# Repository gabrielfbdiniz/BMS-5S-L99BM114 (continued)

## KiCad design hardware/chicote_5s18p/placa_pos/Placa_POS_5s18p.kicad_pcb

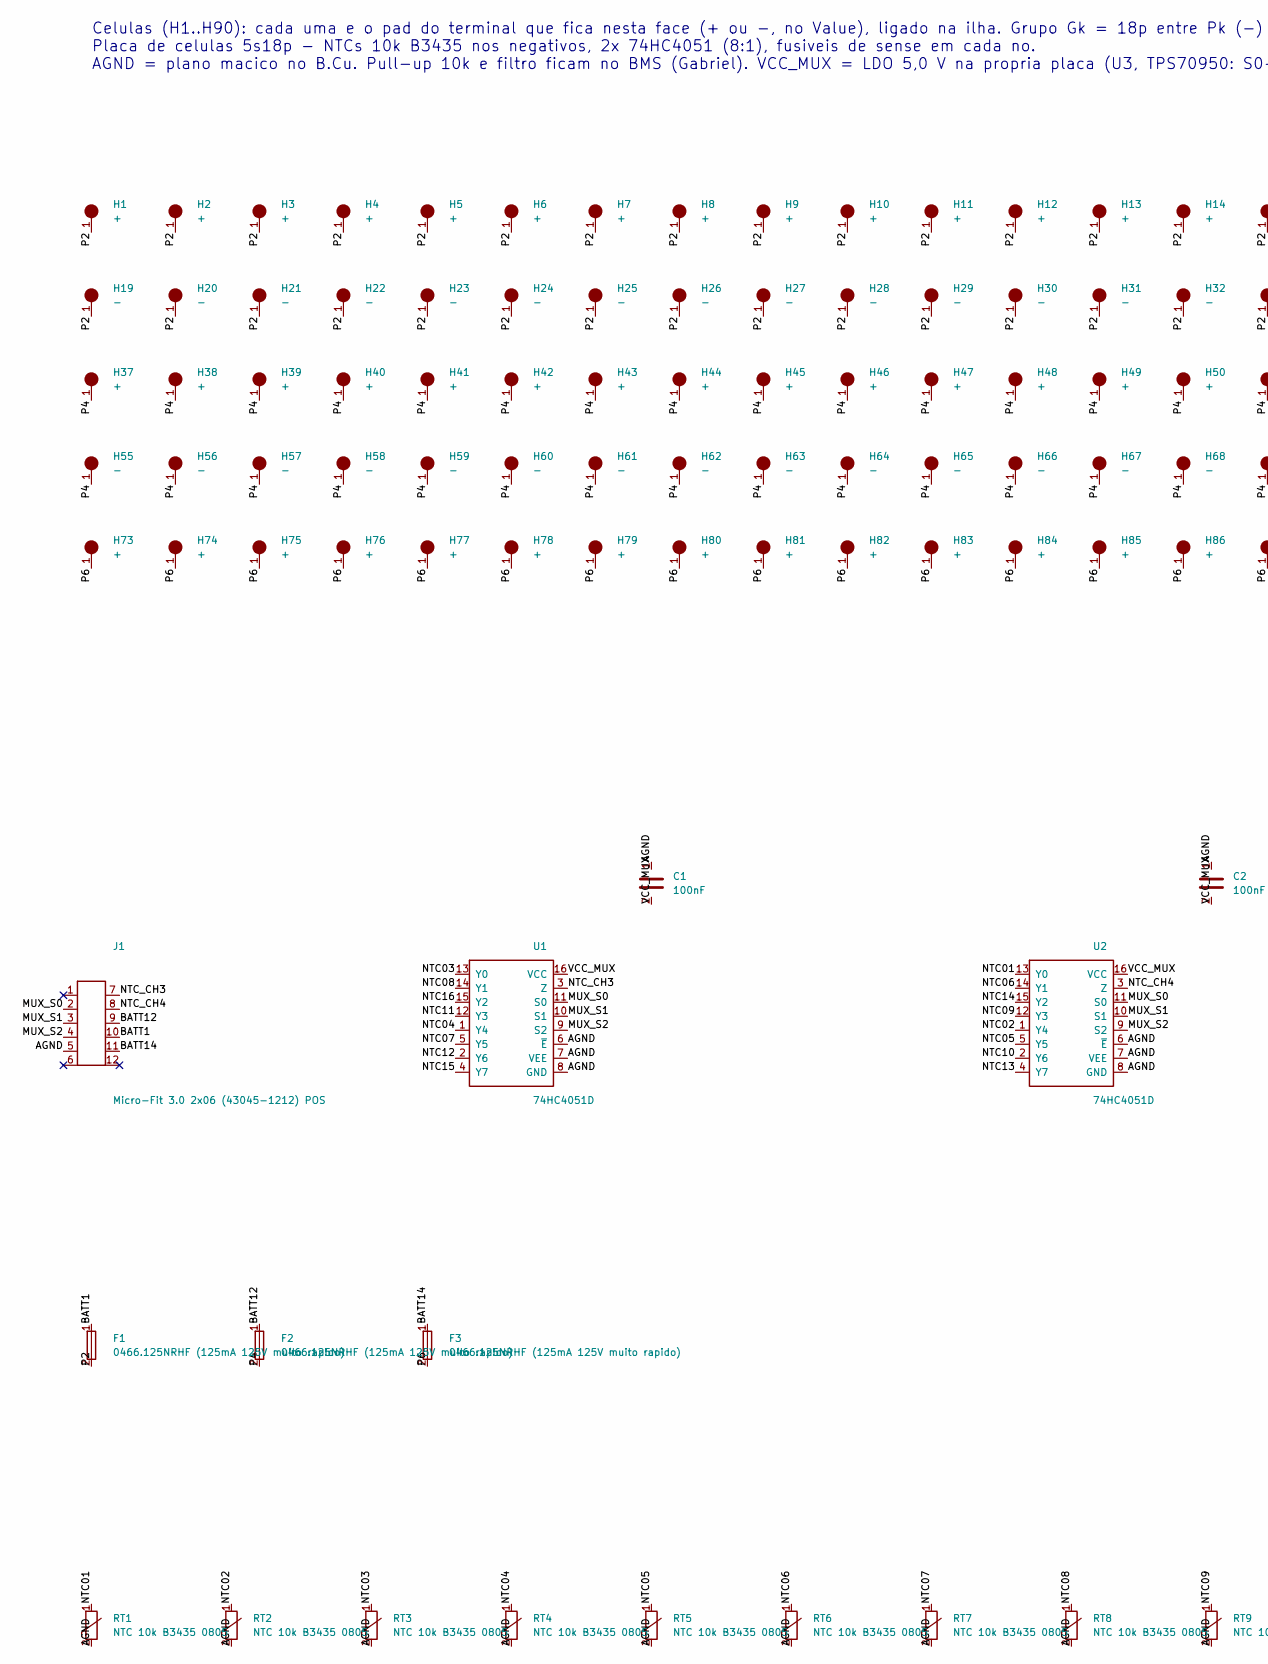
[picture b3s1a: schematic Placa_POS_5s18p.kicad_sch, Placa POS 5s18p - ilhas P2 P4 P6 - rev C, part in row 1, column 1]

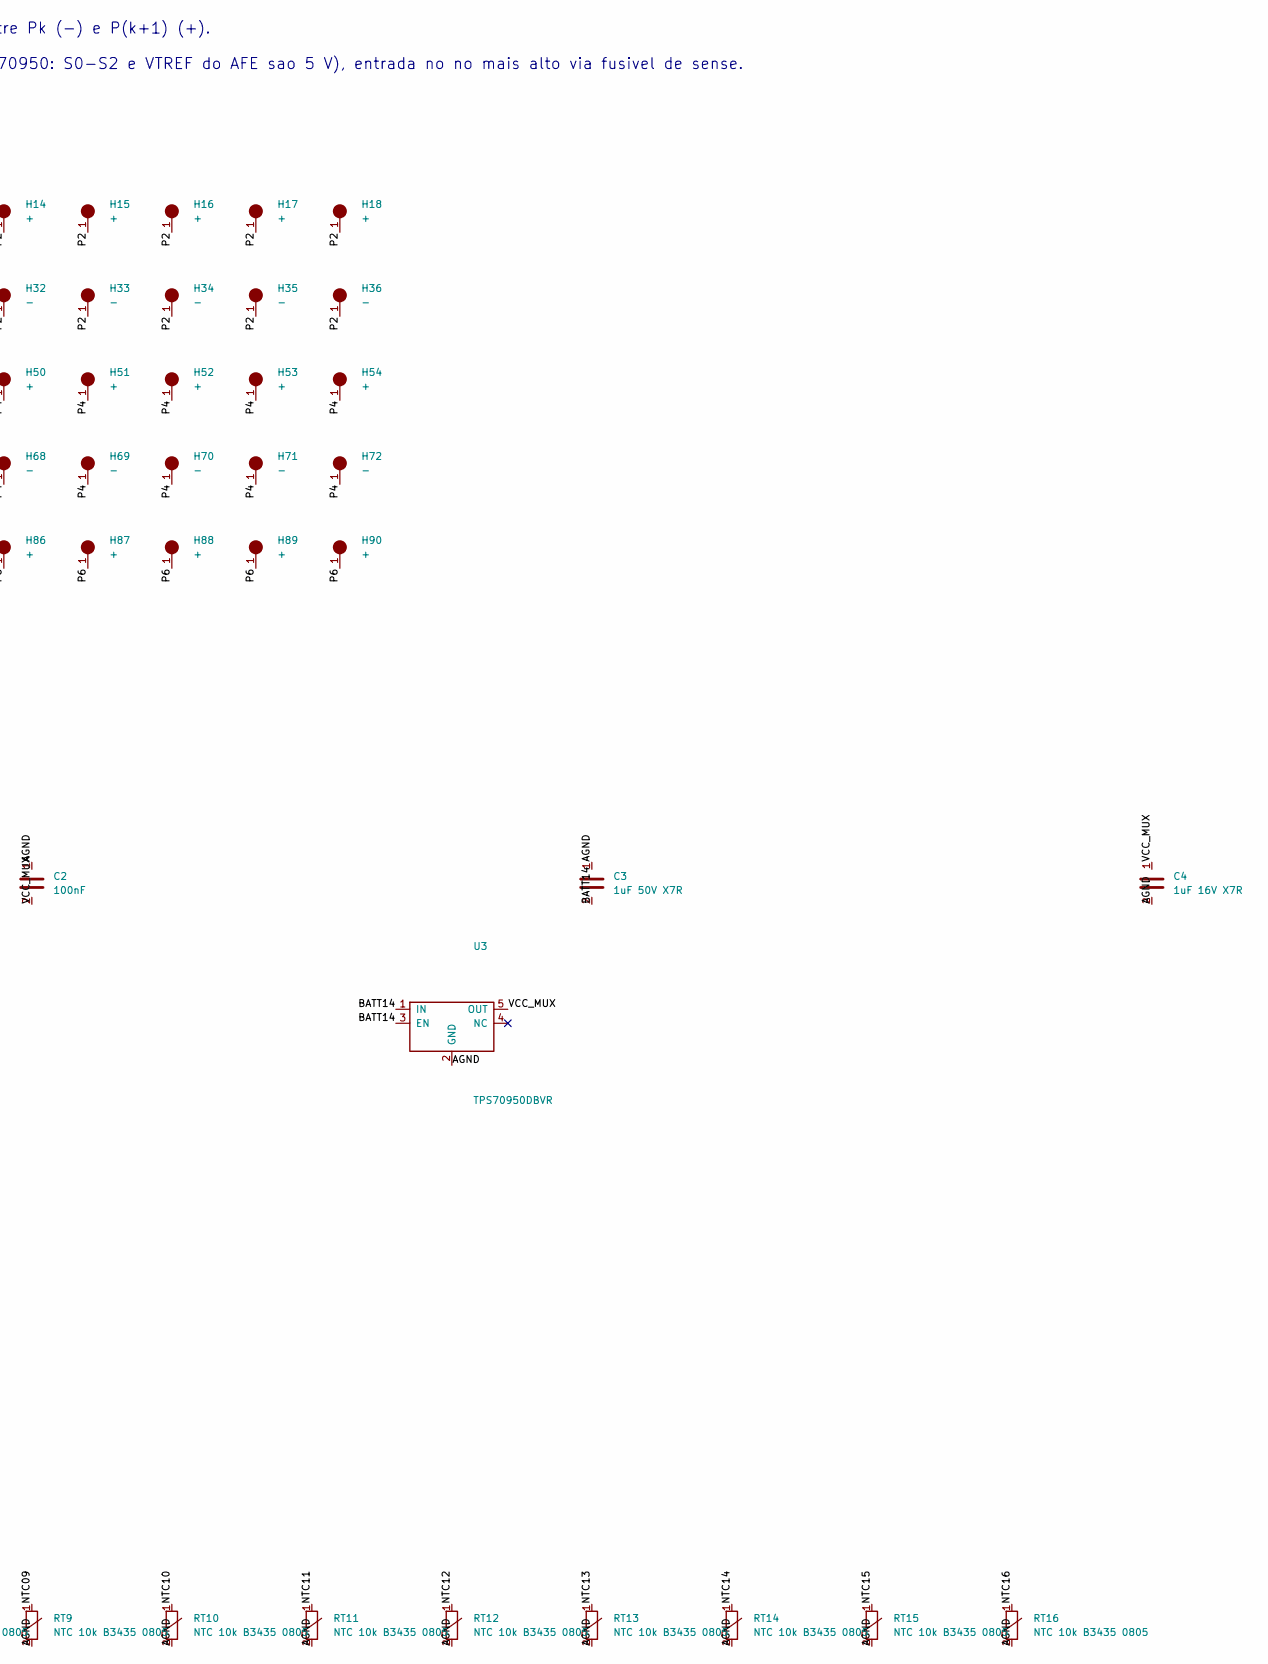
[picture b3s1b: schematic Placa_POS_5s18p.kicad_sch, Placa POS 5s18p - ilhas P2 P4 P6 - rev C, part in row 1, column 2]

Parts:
C1, C2: 100nF; C_0805_2012Metric
C3: 1uF 50V X7R; C_0805_2012Metric
C4: 1uF 16V X7R; C_0805_2012Metric
F1, F2, F3: 0466.125NRHF (125mA 125V muito rapido); Fuse_1206_3216Metric
H1, H2, H3, H4, H5, H6, H7, H8, H9, H10, H11, H12, H13, H14, H15, H16, H17, H18, H37, H38, H39, H40, H41, H42, H43, H44, H45, H46, H47, H48, H49, H50, H51, H52, H53, H54, H73, H74, H75, H76, H77, H78, H79, H80, H81, H82, H83, H84, H85, H86, H87, H88, H89, H90: +; Celula_21700_terminal_POS
H19, H20, H21, H22, H23, H24, H25, H26, H27, H28, H29, H30, H31, H32, H33, H34, H35, H36, H55, H56, H57, H58, H59, H60, H61, H62, H63, H64, H65, H66, H67, H68, H69, H70, H71, H72: -; Celula_21700_terminal_NEG
J1: Micro-Fit 3.0 2x06 (43045-1212) POS; Molex_Micro-Fit_3.0_43045-1212_2x06_P3.00mm_Vertical
RT1, RT2, RT3, RT4, RT5, RT6, RT7, RT8, RT9, RT10, RT11, RT12, RT13, RT14, RT15, RT16: NTC 10k B3435 0805; R_0805_2012Metric
U1, U2: 74HC4051D; SOIC-16_3.9x9.9mm_P1.27mm
U3: TPS70950DBVR; SOT-23-5

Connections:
AGND: C1.1, C2.1, C3.1, C4.2, J1.5, RT1.2, RT2.2, RT3.2, RT4.2, RT5.2, RT6.2, RT7.2, RT8.2, RT9.2, RT10.2, RT11.2, RT12.2, RT13.2, RT14.2, RT15.2, RT16.2, U1.6 (~E), U1.7 (VEE), U1.8 (GND), U2.6 (~E), U2.7 (VEE), U2.8 (GND), U3.2 (GND)
BATT1: F1.1, J1.10
BATT12: F2.1, J1.9
BATT14: C3.2, F3.1, J1.11, U3.1 (IN), U3.3 (EN)
MUX_S0: J1.2, U1.11 (S0), U2.11 (S0)
MUX_S1: J1.3, U1.10 (S1), U2.10 (S1)
MUX_S2: J1.4, U1.9 (S2), U2.9 (S2)
NTC01: RT1.1, U2.13 (Y0)
NTC02: RT2.1, U2.1 (Y4)
NTC03: RT3.1, U1.13 (Y0)
NTC04: RT4.1, U1.1 (Y4)
NTC05: RT5.1, U2.5 (Y5)
NTC06: RT6.1, U2.14 (Y1)
NTC07: RT7.1, U1.5 (Y5)
NTC08: RT8.1, U1.14 (Y1)
NTC09: RT9.1, U2.12 (Y3)
NTC10: RT10.1, U2.2 (Y6)
NTC11: RT11.1, U1.12 (Y3)
NTC12: RT12.1, U1.2 (Y6)
NTC13: RT13.1, U2.4 (Y7)
NTC14: RT14.1, U2.15 (Y2)
NTC15: RT15.1, U1.4 (Y7)
NTC16: RT16.1, U1.15 (Y2)
NTC_CH3: J1.7, U1.3 (Z)
NTC_CH4: J1.8, U2.3 (Z)
P2: F1.2, H1.1, H2.1, H3.1, H4.1, H5.1, H6.1, H7.1, H8.1, H9.1, H10.1, H11.1, H12.1, H13.1, H14.1, H15.1, H16.1, H17.1, H18.1, H19.1, H20.1, H21.1, H22.1, H23.1, H24.1, H25.1, H26.1, H27.1, H28.1, H29.1, H30.1, H31.1, H32.1, H33.1, H34.1, H35.1, H36.1
P4: F2.2, H37.1, H38.1, H39.1, H40.1, H41.1, H42.1, H43.1, H44.1, H45.1, H46.1, H47.1, H48.1, H49.1, H50.1, H51.1, H52.1, H53.1, H54.1, H55.1, H56.1, H57.1, H58.1, H59.1, H60.1, H61.1, H62.1, H63.1, H64.1, H65.1, H66.1, H67.1, H68.1, H69.1, H70.1, H71.1, H72.1
P6: F3.2, H73.1, H74.1, H75.1, H76.1, H77.1, H78.1, H79.1, H80.1, H81.1, H82.1, H83.1, H84.1, H85.1, H86.1, H87.1, H88.1, H89.1, H90.1
VCC_MUX: C1.2, C2.2, C4.1, U1.16 (VCC), U2.16 (VCC), U3.5 (OUT)

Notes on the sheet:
Celulas (H1..H90): cada uma e o pad do terminal que fica nesta face (+ ou -, no Value), ligado na ilha. Grupo Gk = 18p entre Pk (-) e P(k+1) (+). Placa de celulas 5s18p - NTCs 10k B3435 nos negativos, 2x 74HC4051 (8:1), fusiveis de sense em cada no. AGND = plano macico no B.Cu. Pull-up 10k e filtro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

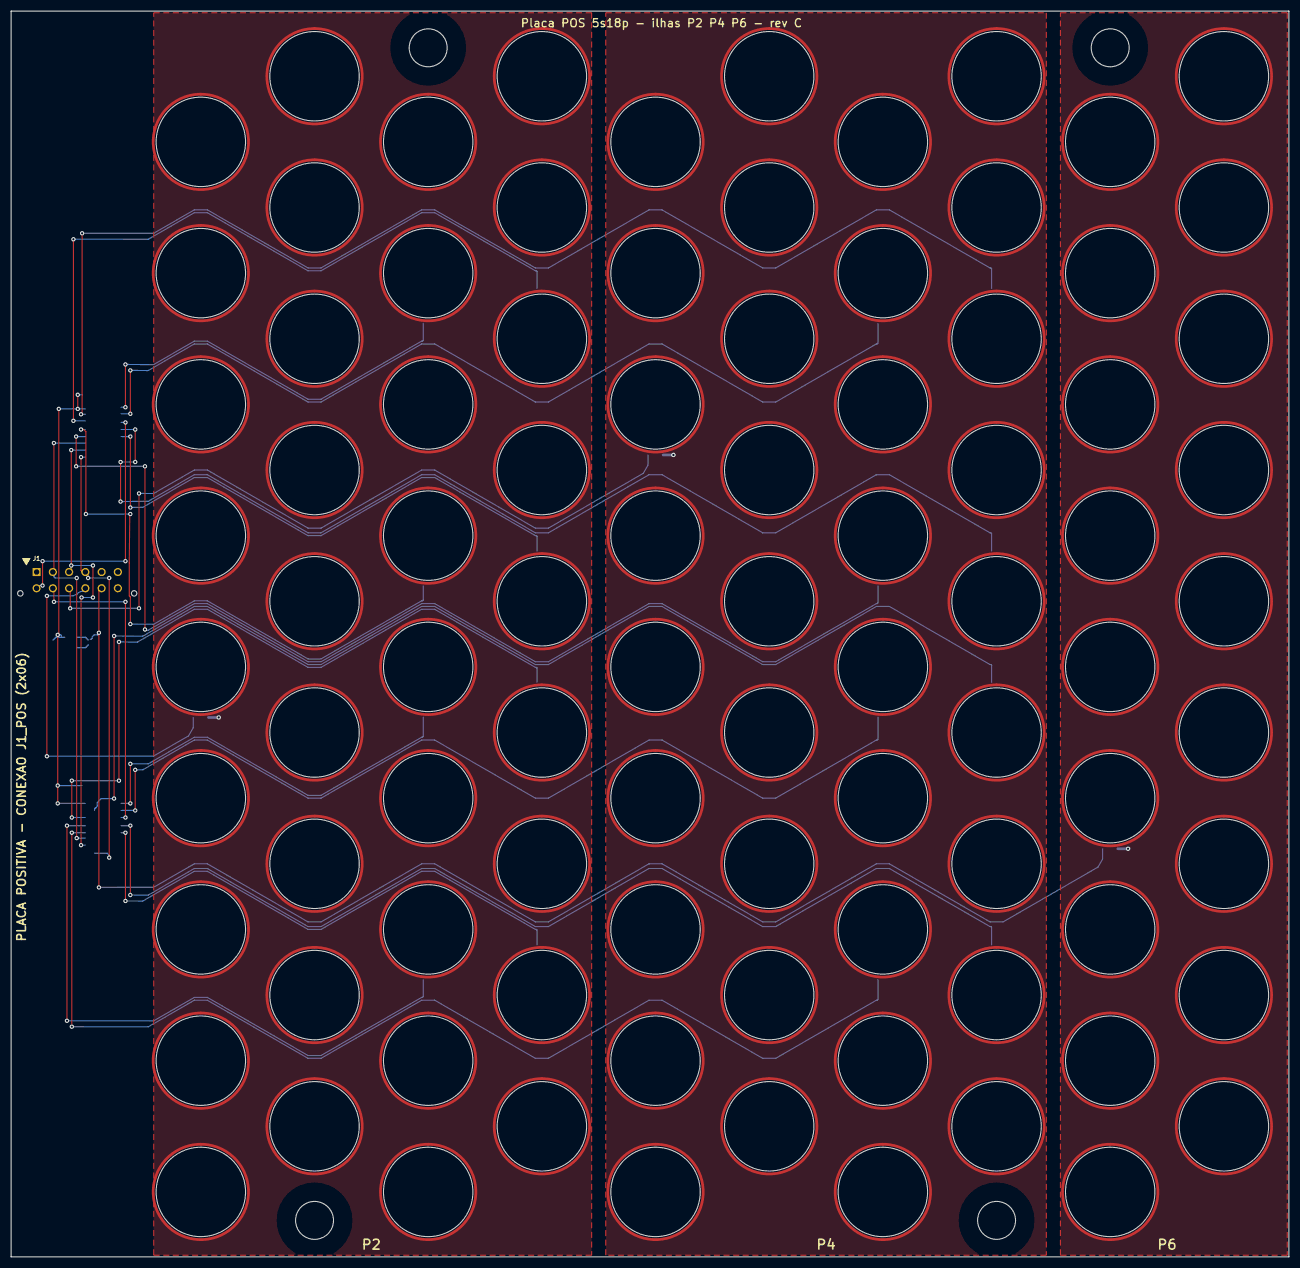
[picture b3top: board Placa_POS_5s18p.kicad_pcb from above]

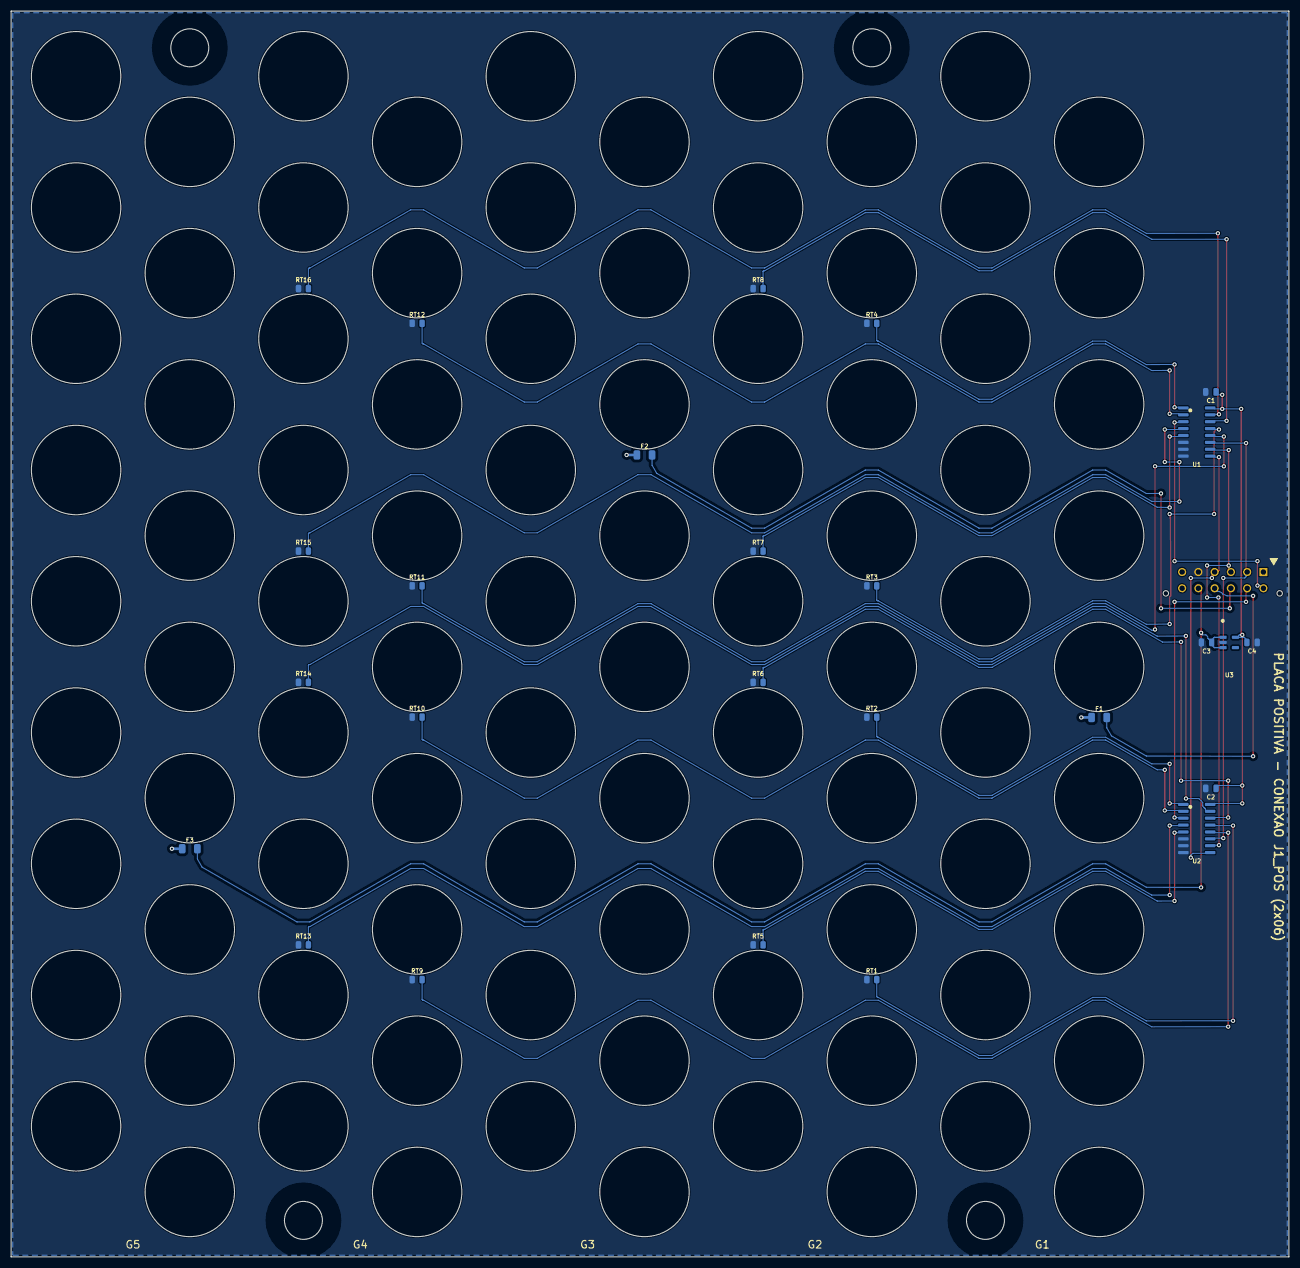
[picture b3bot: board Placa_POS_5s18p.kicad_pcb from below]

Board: 2 copper layers, 235.8 x 229.9 mm, 121 parts (26 on the bottom side), 29 nets.

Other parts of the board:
MH1, MH2, MH3, MH4: M6; Furo_Fixacao_7mm
